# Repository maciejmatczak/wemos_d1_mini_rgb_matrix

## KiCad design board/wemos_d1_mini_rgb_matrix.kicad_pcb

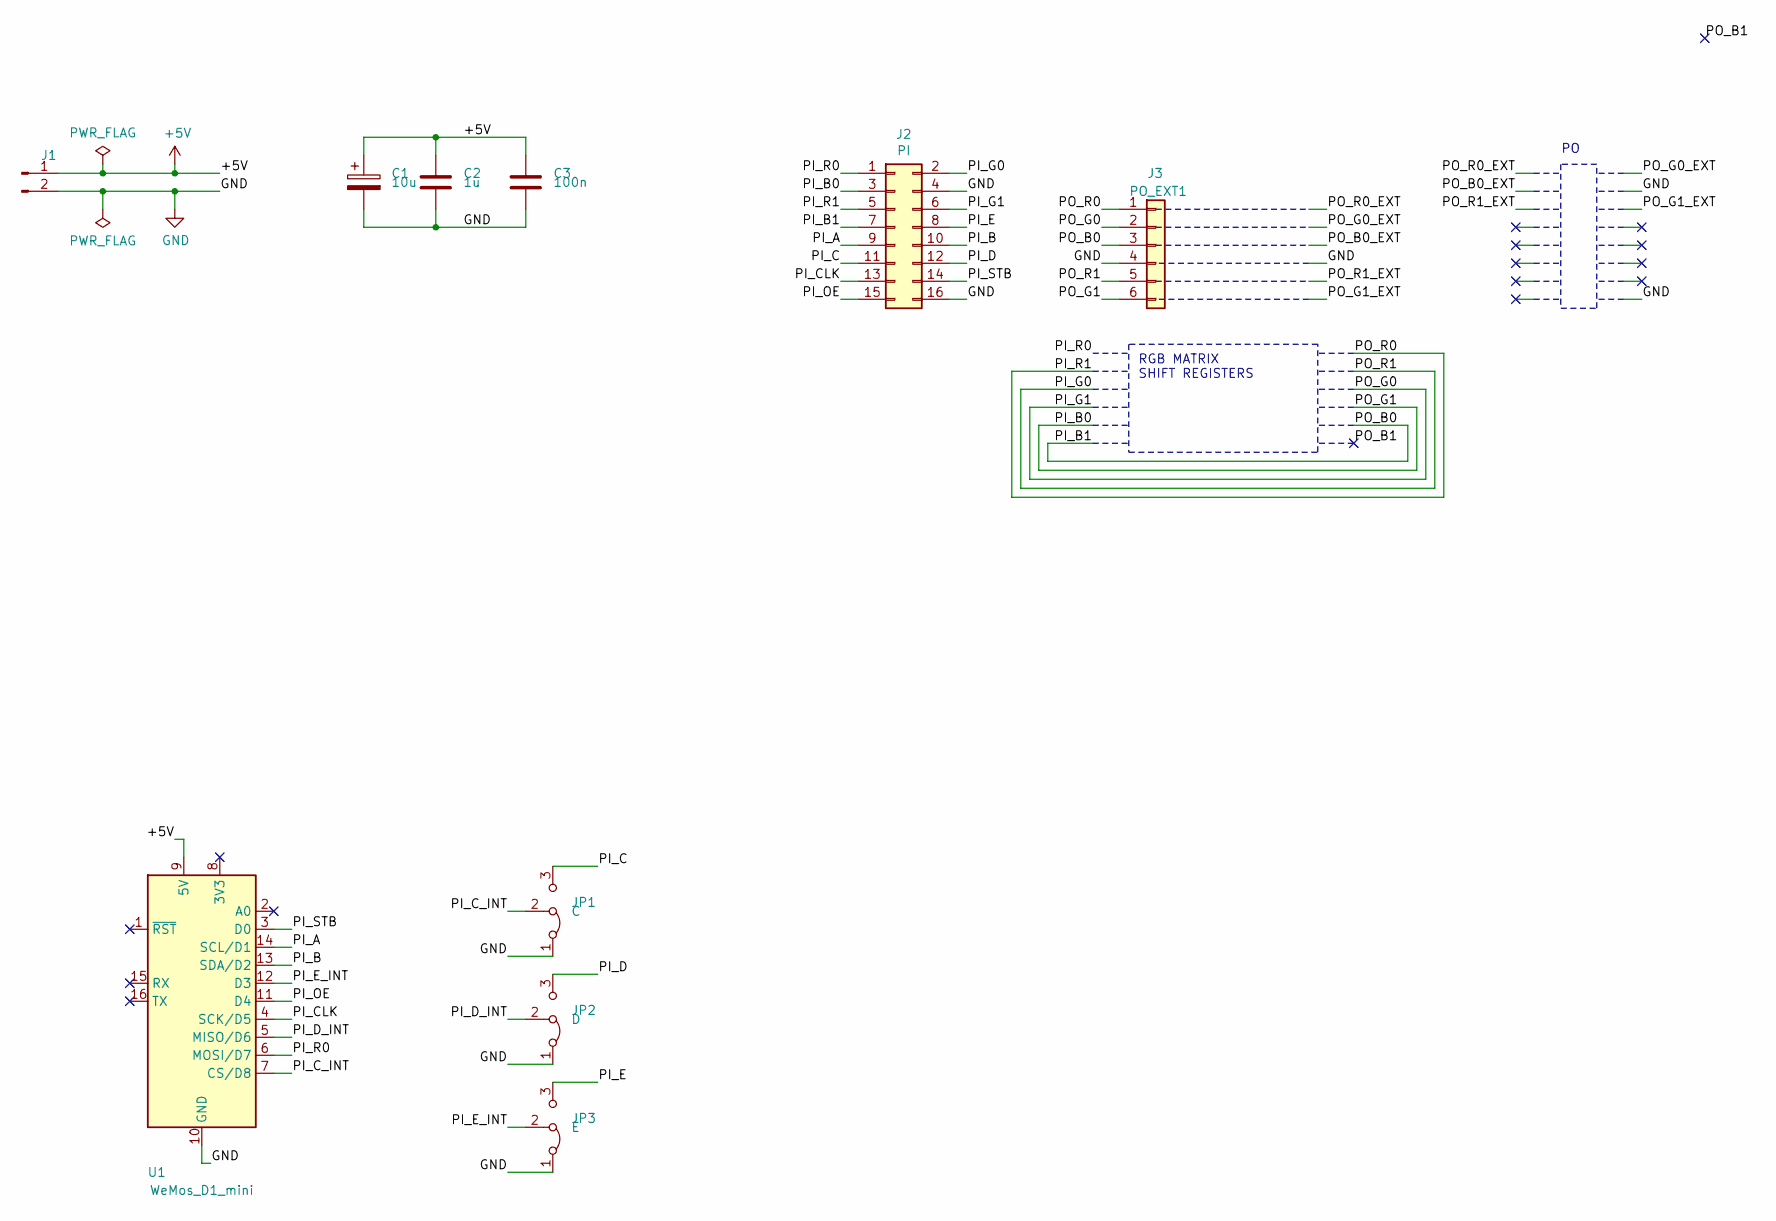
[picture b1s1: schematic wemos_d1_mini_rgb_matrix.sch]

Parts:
C1: 10u; CP_Radial_D4.0mm_P1.50mm
C2: 1u; C_0805_2012Metric_Pad1.15x1.40mm_HandSolder
C3: 100n; C_0805_2012Metric_Pad1.15x1.40mm_HandSolder
J1: Conn_01x02_Male; SolderWirePad_1x02_P3.81mm_Drill1.2mm
J2: PI; PinSocket_2x08_P2.54mm_Vertical
J3: PO_EXT1; PinHeader_1x06_P2.54mm_Vertical
JP1: C; SolderJumper-3_P1.3mm_Open_Pad1.0x1.5mm
JP2: D; SolderJumper-3_P1.3mm_Open_Pad1.0x1.5mm
JP3: E; SolderJumper-3_P1.3mm_Open_Pad1.0x1.5mm
U1: WeMos_D1_mini; WEMOS_D1_mini_light

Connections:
+5V: C1.1, C2.1, C3.1, J1.1, U1.9 (5V)
/PI_A: J2.9, U1.14 (SCL/D1)
/PI_B: J2.10, U1.13 (SDA/D2)
/PI_B0: J2.3, J3.6
/PI_B1: J2.7, J3.3
/PI_C: J2.11, JP1.3 (B)
/PI_CLK: J2.13, U1.4 (SCK/D5)
/PI_C_INT: JP1.2 (C), U1.7 (CS/D8)
/PI_D: J2.12, JP2.3 (B)
/PI_D_INT: JP2.2 (C), U1.5 (MISO/D6)
/PI_E: J2.8, JP3.3 (B)
/PI_E_INT: JP3.2 (C), U1.12 (D3)
/PI_G0: J2.2, J3.5
/PI_G1: J2.6, J3.2
/PI_OE: J2.15, U1.11 (D4)
/PI_R0: J2.1, U1.6 (MOSI/D7)
/PI_R1: J2.5, J3.1
/PI_STB: J2.14, U1.3 (D0)
GND: C1.2, C2.2, C3.2, J1.2, J2.4, J2.16, J3.4, JP1.1 (A), JP2.1 (A), JP3.1 (A), U1.10 (GND)

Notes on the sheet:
RGB MATRIX SHIFT REGISTERS

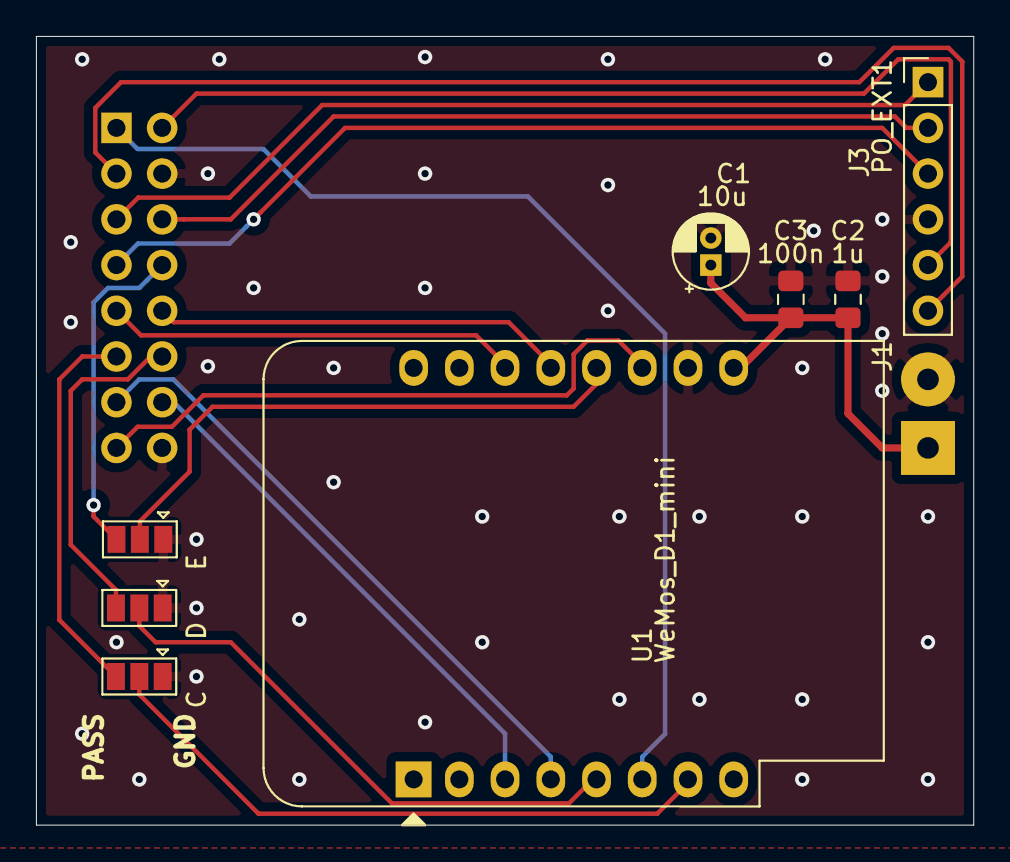
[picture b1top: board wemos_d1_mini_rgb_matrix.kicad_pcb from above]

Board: 2 copper layers, 52.1 x 43.8 mm, 10 parts (1 on the bottom side), 19 nets.

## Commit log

2019-05-17 Adding board files on first design iteration
2019-05-17 Add global gitignore
2019-05-17 Add tasks.py with "plot" and "clean" tasks
2019-05-17 Add plot script for KiCAD
2019-05-17 import cleanup
2019-05-17 Remove vscode settings.json from exclusion
2019-05-17 Create LICENSE
2019-06-09 Update gitignore
2019-06-09 Trying out FreeCAD way
2019-06-09 Move to Fusion 360 design
2019-06-09 Add F360 model files, images and description
